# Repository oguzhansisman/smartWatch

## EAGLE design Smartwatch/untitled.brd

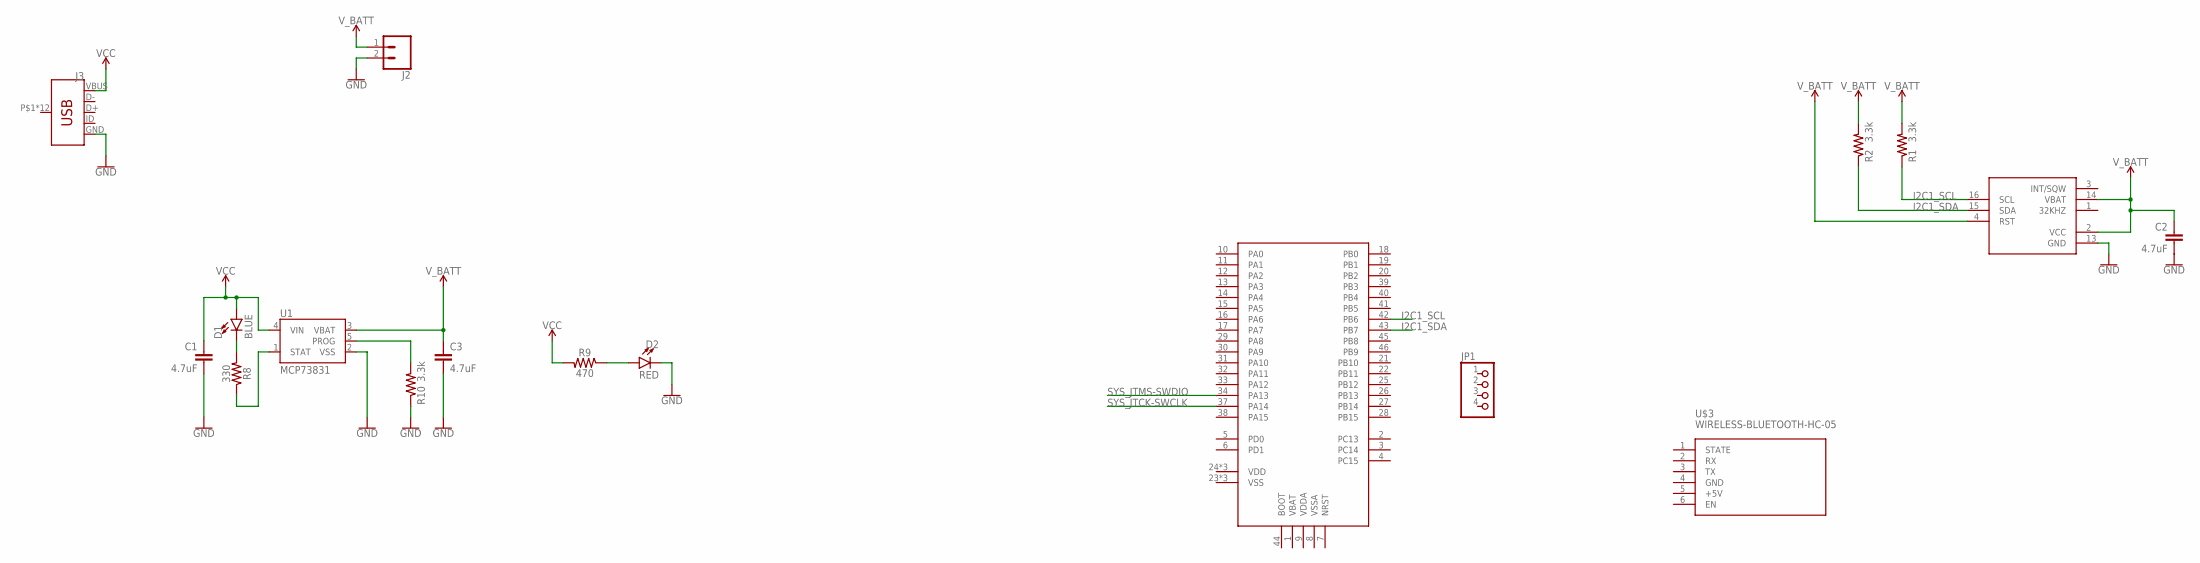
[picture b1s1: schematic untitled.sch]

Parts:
C1, C2, C3: 4.7uF; 0603
D1: BLUE; LED-0603
D2: RED; LED-0603
J2: CONN_021X02_NO_SILK; 1X02_NO_SILK
J3: USB_MICRO-B_HALF_PTH; USB-MICROB-PTH
JP1: PINHD-1X4; 1X04
R1, R2, R10: 3.3k; 0603
R8: 330; 0603
R9: 470; 0603
U1: MCP73831; SOT23-5
U$1: STM32F103C8T6; LQFP48
U$2: DS3231; SO-16
U$3: WIRELESS-BLUETOOTH-HC-05

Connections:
+5V: U$3.5 (+5V)
GND: C1.2, C2.2, C3.2, D2.C, J2.2, J3.GND, R10.1, U1.2 (VSS), U$2.13 (GND), U$3.4 (GND)
I2C1_SCL: R1.1, U$1.42 (PB6), U$2.16 (SCL)
I2C1_SDA: R2.1, U$1.43 (PB7), U$2.15 (SDA)
unnamed: R8.1, U1.1 (STAT)
unnamed: D1.C, R8.2
unnamed: R10.2, U1.5 (PROG)
unnamed: D2.A, R9.1
SYS_JTCK-SWCLK: U$1.37 (PA14)
SYS_JTMS-SWDIO: U$1.34 (PA13)
VCC: C1.1, D1.A, J3.VBUS, R9.2, U1.4 (VIN)
V_BATT: C2.1, C3.1, J2.1, R1.2, R2.2, U1.3 (VBAT), U$2.2 (VCC), U$2.4 (RST), U$2.14 (VBAT)

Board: 2 copper layers, 17 parts (0 on the bottom side), 9 nets, no tracks yet.

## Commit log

2020-12-29 smartWatch_v.0.1
    RTC okunup menü geliştirilmelerine başlandı
2020-12-29 Menü Bugları giderildi
    Guzel calisiyor
2020-12-29 Nabiz menü tamamlandı
    nabiz menüsüne girip cikilabiliyor
2020-12-29 smartWatch_v.0.2
    saat menüsü büyük oranda tamamlandı
2021-01-01 task yapıları oluşturuldu
    düzgün çalışıyor
2021-01-01 smartWatch_v.03
2021-01-01 Saat ayarlama fonksiyonları eklendi
2021-01-01 smartWatch_v.1.0
    -Eklenen bütün foksiyonlar denendi sorunsuz çalışıyor.
    -OLED ekran ve RTC modülü farklı çevrebiirmlere taşındı.
2021-01-04 Proje hazırlık için fonksiyon ve yapı açıklamaları yazıldı
2021-02-21 Smartwatch Eagle Files
    İşemci, ds3231, batarya şarj devresi, footprint ve şematikler hazır

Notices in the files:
parts and their libraries:
SparkFun-Capacitors: Licensing: Creative Commons ShareAlike 4.0 International - https://creativecommons.org/licenses/by-sa/4.0
diy-modules: Released under the Creative Commons Attribution 4.0 International License: http://creativecommons.org/licenses/by/4.0
